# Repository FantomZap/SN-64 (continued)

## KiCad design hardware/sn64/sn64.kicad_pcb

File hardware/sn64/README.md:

# SN 64 KiCad schematic draft

Open **[sn64.kicad_pro](sn64.kicad_pro)** in KiCad 10, then open the schematic. The root (rev `0.4-r3`, A2) holds both cartridge connectors and five child sheets, wired by same-name root labels (the shared net-name contract in [system-integration.md](../../docs/design/system-integration.md#schematic-integration-round-3-2026-09-29)):

- page 2: the [USB programmer child sheet](usb-programmer.kicad_sch) (exports USB_VBUS, USB_3V3, USB_CC1/CC2, jtag_tck/tms/tdi/tdo, TARGET_VREF; R101/R102 DNP because the power sheet's TUSB320 presents Rd);
- page 3: the [SNES cartridge interface child sheet](cart-interface.kicad_sch) (rev 0.3.1-cart: 5 V/3.3 V translators, reset/IRQ/CIC paths, per-pin CIC data translators; see [notes](../../docs/design/cart-interface-schematic.md));
- page 4: the [FPGA child sheet](fpga.kicad_sch) (rev 0.5-fpga, no HDMI pins, designators 4xx: LFE5U-85F CABGA381 with all 381 balls assigned, W25Q128JVSIQ configuration flash, JTAG, SN74CB3Q3384A N64 bus switches; see [notes](../../docs/design/fpga-schematic.md)). Its pin table also generates [interfaces/fpga-pin-map.csv](interfaces/fpga-pin-map.csv) and [fpga/constraints/sn64_board.lpf](../../fpga/constraints/sn64_board.lpf);
- page 5: the [power child sheet](power.kicad_sch) (designators 3xx: host/USB eFuse priority mux, TUSB320, TPS63070 5V_PRE, three TLV62569 FPGA rails, default-off cartridge eFuse and interface switch, monitors; see [notes](../../docs/design/power-schematic.md));
- page 6: the [clock/cartridge-audio child sheet](av-clock.kicad_sch) (draft 0.2-av, designators 7xx: Si5351A + 25 MHz crystal, 25 MHz FPGA oscillator, PCM1808 I2S-master cartridge-audio ADC; the HDMI output of draft 0.1-av was removed on 2026-09-29; see [notes](../../docs/design/av-clock-schematic.md)).

The [PDF](exports/sn64-interface-draft.pdf) is a review export of all six pages; the round-3 export was not visually inspected (no rasteriser available). Project-local libraries hold the symbols KiCad does not ship. It is not a complete electrical design or a manufacturing package.

The SNES socket now lives on its own small board: **[../sn64-socket/](../sn64-socket/)** (generated by [tools/split_socket_board.py](tools/split_socket_board.py); design note [mechanical-architecture.md](../../docs/design/mechanical-architecture.md)). On this main board, J2 is the 2x40 2.00 mm joint header. Check both boards with `tools/verify_socket_joint.py` (and `--negative-test`).

**Board (first draft, 2026-09-29):** [sn64.kicad_pcb](sn64.kicad_pcb) is generated by [tools/build_main_pcb.py](tools/build_main_pcb.py): 6 layers, 1.2 mm, PCBWay-compatible rules, the SummerCart64 lower outline extended to 70 mm above the tongue shoulders, all 410 parts imported with their 530 nets and a connectivity-pulled placement inside block zones (N64 interface at the bottom, FPGA centred with its decoupling underneath, translators under the top joint header with their resistor arrays beneath them, power/USB left, clock/audio right; small passives on the bottom side). DRC after placement (rebuilt 2026-09-29 without the HDMI parts): 0 real errors; the only reports are the USB-C receptacle pads at the board edge (by design; rule exception in `sn64.kicad_dru`) and the N64 fingers' shared solder-mask opening (SummerCart64 footprint).

**Routing draft (2026-09-30):** the tracked board now carries a first autorouted draft ([notes](../../docs/design/pcb-routing.md)): FPGA rotated 180° so its N64 bank faces the bus switches, 240 dog-bone fan-out vias, GND plane on In1, 3.3 V plane on In3, 1.1 V island on In4, signals routed by KiCadRoutingTools (Rust A*, run 2), 157 plane vias, outer GND pours. DRC: no shorts, crossings, clearance or hole violations. **Still open:** 75 signal/power nets (95 connections, mostly in the translator row) and 219 plane pads without a via ([validation/pcb-open-connections.json](validation/pcb-open-connections.json)). Tools: [tools/prepare_route.py](tools/prepare_route.py), [tools/add_plane_vias.py](tools/add_plane_vias.py), [tools/finish_route.py](tools/finish_route.py), [tools/fab-pcbway.txt](tools/fab-pcbway.txt). Rerunning `build_main_pcb.py --force` regenerates the placement and discards this routing. Renders: [top](exports/sn64-pcb-draft-top.png), [bottom](exports/sn64-pcb-draft-bottom.png). Nothing is routed yet; the placement is a starting point, not a reviewed layout.

## What is present

| Item | Contents |
|---|---|
| J1 | 50-contact N64 edge, intended for both original N64 and M64 |
| J2 | Full 62-contact SNES/SFC female socket, including outer contacts and analog audio |
| USB child sheet | J101 JAE USB-C, DNP CC resistors (the power sheet's TUSB320 presents Rd), data/CC ESD arrays, AP2112K-3.3 bridge regulator, FT232HL revision C, 12 MHz crystal, optional DNP EEPROM, SN74AXC4T774 JTAG isolation and J102 target-side service header |
| Symbol library | Editable native KiCad symbols, numbered from the checked pin maps |
| Footprint library | Sanni female-socket and SummerCart64 N64 edge references; local USB component footprints including the reused JAE receptacle geometry |
| Pin maps | [N64](interfaces/n64-pin-map.csv), [SNES](interfaces/snes-pin-map.csv) and [USB circuit nets](interfaces/usb-programmer-net-map.csv) |
| FPGA, power, A/V sheets | See the page list above; authored by [add_fpga_sheet.py](tools/add_fpga_sheet.py), [add_power_sheet.py](tools/add_power_sheet.py) and [add_av_clock_sheet.py](tools/add_av_clock_sheet.py) (deterministic, refuse to overwrite without `--force`), checked by [verify_fpga_sheet.py](tools/verify_fpga_sheet.py), [verify_power_sheet.py](tools/verify_power_sheet.py) and [verify_av_clock_sheet.py](tools/verify_av_clock_sheet.py) |
| Validation | Exported netlist, ERC report, per-sheet checks (interface 31, USB 69, cartridge 20, FPGA 14, power 23, A/V 27) and the [root connectivity check](tools/verify_root_connectivity.py) (4 checks over 141 contract names) |

`GND` is the only net that directly crosses the USB/host-connector boundary. `HOST_3V3`, `HOST_12V`, `SNES_5V_CART`, `USB_VBUS`, `USB_3V3` and `TARGET_VREF` are distinct nets. USB_VBUS also feeds the power sheet's default-off USB input (U302, enabled only when the TUSB320 U301 reports at least 1.5 A and USB_3V3 is present); `TARGET_VREF` comes from FPGA_3V3 through R414 on the FPGA sheet and is not a USB target-power output. The N64 edge reaches the FPGA only through the host-gated bus switches; N64_AUDIO_L/R and the reserved edge contacts stay unconnected. `_N` in net names denotes active low; the cartridge symbols retain the source maps' slash notation.

Connector pins deliberately have the ordinary passive connector type. The CSV and [electrical notes](../../docs/design/snes-interface-notes.md), rather than these pin types, define endpoint direction and special handling. ERC cannot establish drive ownership, voltage tolerance or timing at these pending interfaces.

The USB bridge uses MPSSE JTAG with ACBUS6 controlling the translator's pulled-up, default-disabled `/OE`. The documented host command must include `--status-pin 14`. Its target JTAG nets now reach the ECP5's dedicated JTAG balls on the FPGA sheet (round 3); the configuration flash is loaded through the FPGA. The [programming architecture](../../docs/design/usb-programming-architecture.md) records blank-EEPROM startup, power isolation, persistent-loading requirements and the remaining tests. [Connector and crystal notes](../../docs/design/usb-connector-mechanics.md) record the source geometry and provisional 11 pF crystal load capacitors.

## Reused geometry and its limits

The SNES footprint retains all 62 pads, 2.5 mm ordinary pitch, two 7.5 mm gaps per row, 5 mm row separation, 1.524 mm pads and 0.762 mm drills. A specific purchasable socket, body dimensions and mounting details still need approval before board layout.

The N64 footprint preserves all 50 source pads, 2.5 mm pitch and 1.5 x 7 mm copper dimensions. Pads 1-25 remain on B.Cu and 26-50 on F.Cu. Its origin corresponds to source board coordinates (150,125), so pads are at local Y=6 mm. Six retained `Edge.Cuts` segments form the open lower connector profile, ending at local (±32.25,0) with its bottom at Y=10.5 mm. **Do not duplicate these cuts** when extending the board outline. The footprint does not include a complete board perimeter, mounting holes, layer stack or bevel. Those are separate controlled dimensions in [the geometry record](../../docs/dimensions.md). No generic KiCad board thickness should be treated as the connector thickness.

See [THIRD_PARTY.md](THIRD_PARTY.md), [cartridge provenance](libraries/provenance.json) and [USB provenance](libraries/usb-provenance.json) for sources, modifications and retained licenses. All 24 USB footprint pad objects also match the source geometry in the [footprint review](validation/usb-footprint-review.json). The copies of upstream footprints are reference assets, not a fit-tested SN 64 board.

## Validation and reproducibility

KiCad 10.0.6 exports the six-page schematic to XML and PDF. The round-3 PDF was **not** visually inspected (no rasteriser on this machine); earlier two-sheet exports were. The saved ERC report contains **zero errors** and 10 warnings: 5 `isolated_pin_label` on the reserved N64 edge labels (N64_AUDIO_L/R, N64_KEY1/KEY2_RESERVED, N64_VIDEO_SYNC_RESERVED) and 5 `pin_to_pin` (cartridge U206 unused B4-B8 on the flagged GND). On the integrated root: `verify_cart_interface.py` 20/20 (negative 6/6), `verify_power_sheet.py` 23/23 (negative 11/11), `verify_av_clock_sheet.py` 30/30 (negative 12/12), `verify_fpga_sheet.py` **12/13** (negative 10/10; the failing check is `efuse_fault_n`, a 5V_PRE divider on ball K4, an open owner decision in [system-integration.md](../../docs/design/system-integration.md)), `verify_root_connectivity.py` 4/4 (negative 4/4). The schematic is incomplete and is not an ERC-clean release. Rerun checks as circuitry changes.

The [independent validation script](tools/verify_interfaces.py) checks the exported connector pin/net assignments against the separately researched maps, rejects accidental cross-domain connections, and compares both footprints against the original downloaded sources. The corresponding [result](validation/interface-check.json) and [review](validation/interface-review.md) record the result and remaining limitations.

The saved reports record **30 cartridge-interface checks passed and 69 USB checks passed, with zero failed checks** (the USB set now also checks the DNP CC resistors and the CC/VBUS/USB_3V3/JTAG/TARGET_VREF exports). The [USB validator](tools/verify_usb_programmer.py) independently exports the schematic and compares it with fixed manufacturer pin tables, checking all USB component pins, rail separation, CC/data/ESD connections, bridge support, JTAG directions and disabled startup. See its [result](validation/usb-check.json) and [review](validation/usb-review.md). These are static checks; no USB enumeration, clock measurement, suspend-current measurement, programming, cold boot, electrical protection or compatibility test has been performed on SN 64 hardware.

To regenerate review files after editing, run these from this directory with KiCad's CLI on PATH:

```powershell
kicad-cli sch export netlist --format kicadxml -o validation/sn64.xml sn64.kicad_sch
kicad-cli sch export pdf -o exports/sn64-interface-draft.pdf sn64.kicad_sch
kicad-cli sch erc --format json --output validation/erc.json --exit-code-violations sn64.kicad_sch
```

The per-sheet and root checks, from the repository root with KiCad's Python (each also takes `--negative-test`, except the interface and USB validators):

```powershell
$py = 'C:\Program Files\KiCad\10.0\bin\python.exe'; $cli = 'C:\Program Files\KiCad\10.0\bin\kicad-cli.exe'
& $py hardware/sn64/tools/verify_interfaces.py --source-root . --kicad-cli $cli
& $py hardware/sn64/tools/verify_usb_programmer.py --kicad-cli $cli
& $py hardware/sn64/tools/verify_cart_interface.py --kicad-cli $cli
& $py hardware/sn64/tools/verify_fpga_sheet.py --kicad-cli $cli --lattice-csv <ECP5U-85 pinout CSV> --datasheets <dir>
& $py hardware/sn64/tools/verify_power_sheet.py --kicad-cli $cli
& $py hardware/sn64/tools/verify_av_clock_sheet.py --project hardware/sn64 --kicad-cli $cli
& $py hardware/sn64/tools/verify_root_connectivity.py --kicad-cli $cli
```

The initial authoring script, [create_interface_draft.py](tools/create_interface_draft.py), uses KiCad's Python and downloaded upstream sources. It refuses to replace an existing schematic unless explicitly passed `--force`. Once circuit editing begins, edit the native KiCad files; do not regenerate the initial sheet over the circuit work.

[add_usb_programmer.py](tools/add_usb_programmer.py) records how the initial USB sheet was authored from the reference designs and installed KiCad libraries. It also refuses to replace its sheet without `--force`; use native KiCad editing for subsequent development. Regeneration requires `--source-root <original-project-with-downloads>` and `--kicad-share <KiCad-share-directory>`, and intentionally replaces the entire USB child sheet when forced.

## Remaining integration

**Required in the first revision:** a side-mounted USB-C data/programming port and matching enclosure opening, supporting initial firmware/FPGA loading, updates and recovery without successful host-console boot. The bridge and service-access circuit now exists; the complete programming path remains pending target integration and testing. Final side-port placement, cable access and shell clearances remain mechanical work.

1. Build the power budget for the FPGA, memory, digital A/V and real cartridges on both hosts. The M64 reference annotates a 500 mA cartridge limiter; that is not a guaranteed SN 64 allowance. There is no 5 V N64 edge supply. Select input power, no-backfeed paths and default-off protected cartridge power from the actual budget.
2. Adapt the sd2snes translator circuit using the [reuse review](../../docs/design/translation-reuse-review.md). Reverse address/strobe ownership for a console endpoint; define enable, read/write turnaround and power-off behavior for the exact part. Separately implement IRQ/reset, CIC, expansion and analog audio.
3. Integrate the reusable SNES FPGA core, physical cartridge bridge and N64 endpoint. Select FPGA/package and memory only after resource, I/O, clock and timing evidence. Connect the USB programmer to the selected target and persistent configuration storage, define programming power/boot straps and package the loading/recovery software. Add health monitoring and A/V, then review the complete schematic.
4. Place and route a PCB with the verified mechanical constraints; develop the FreeCAD enclosure around that assembly. Produce PCBWay files after electrical review and prototype/fit validation.

These are stages of the full specification. PAL, protection, save integrity, telemetry, factory testing and all remaining specification targets are retained. Video and audio go to the console over the cartridge bus (console video path); the adapter has no output of its own. No PCB layout, FPGA bitstream, working adapter, print-ready shell or PCBWay manufacturing release is included in this revision.

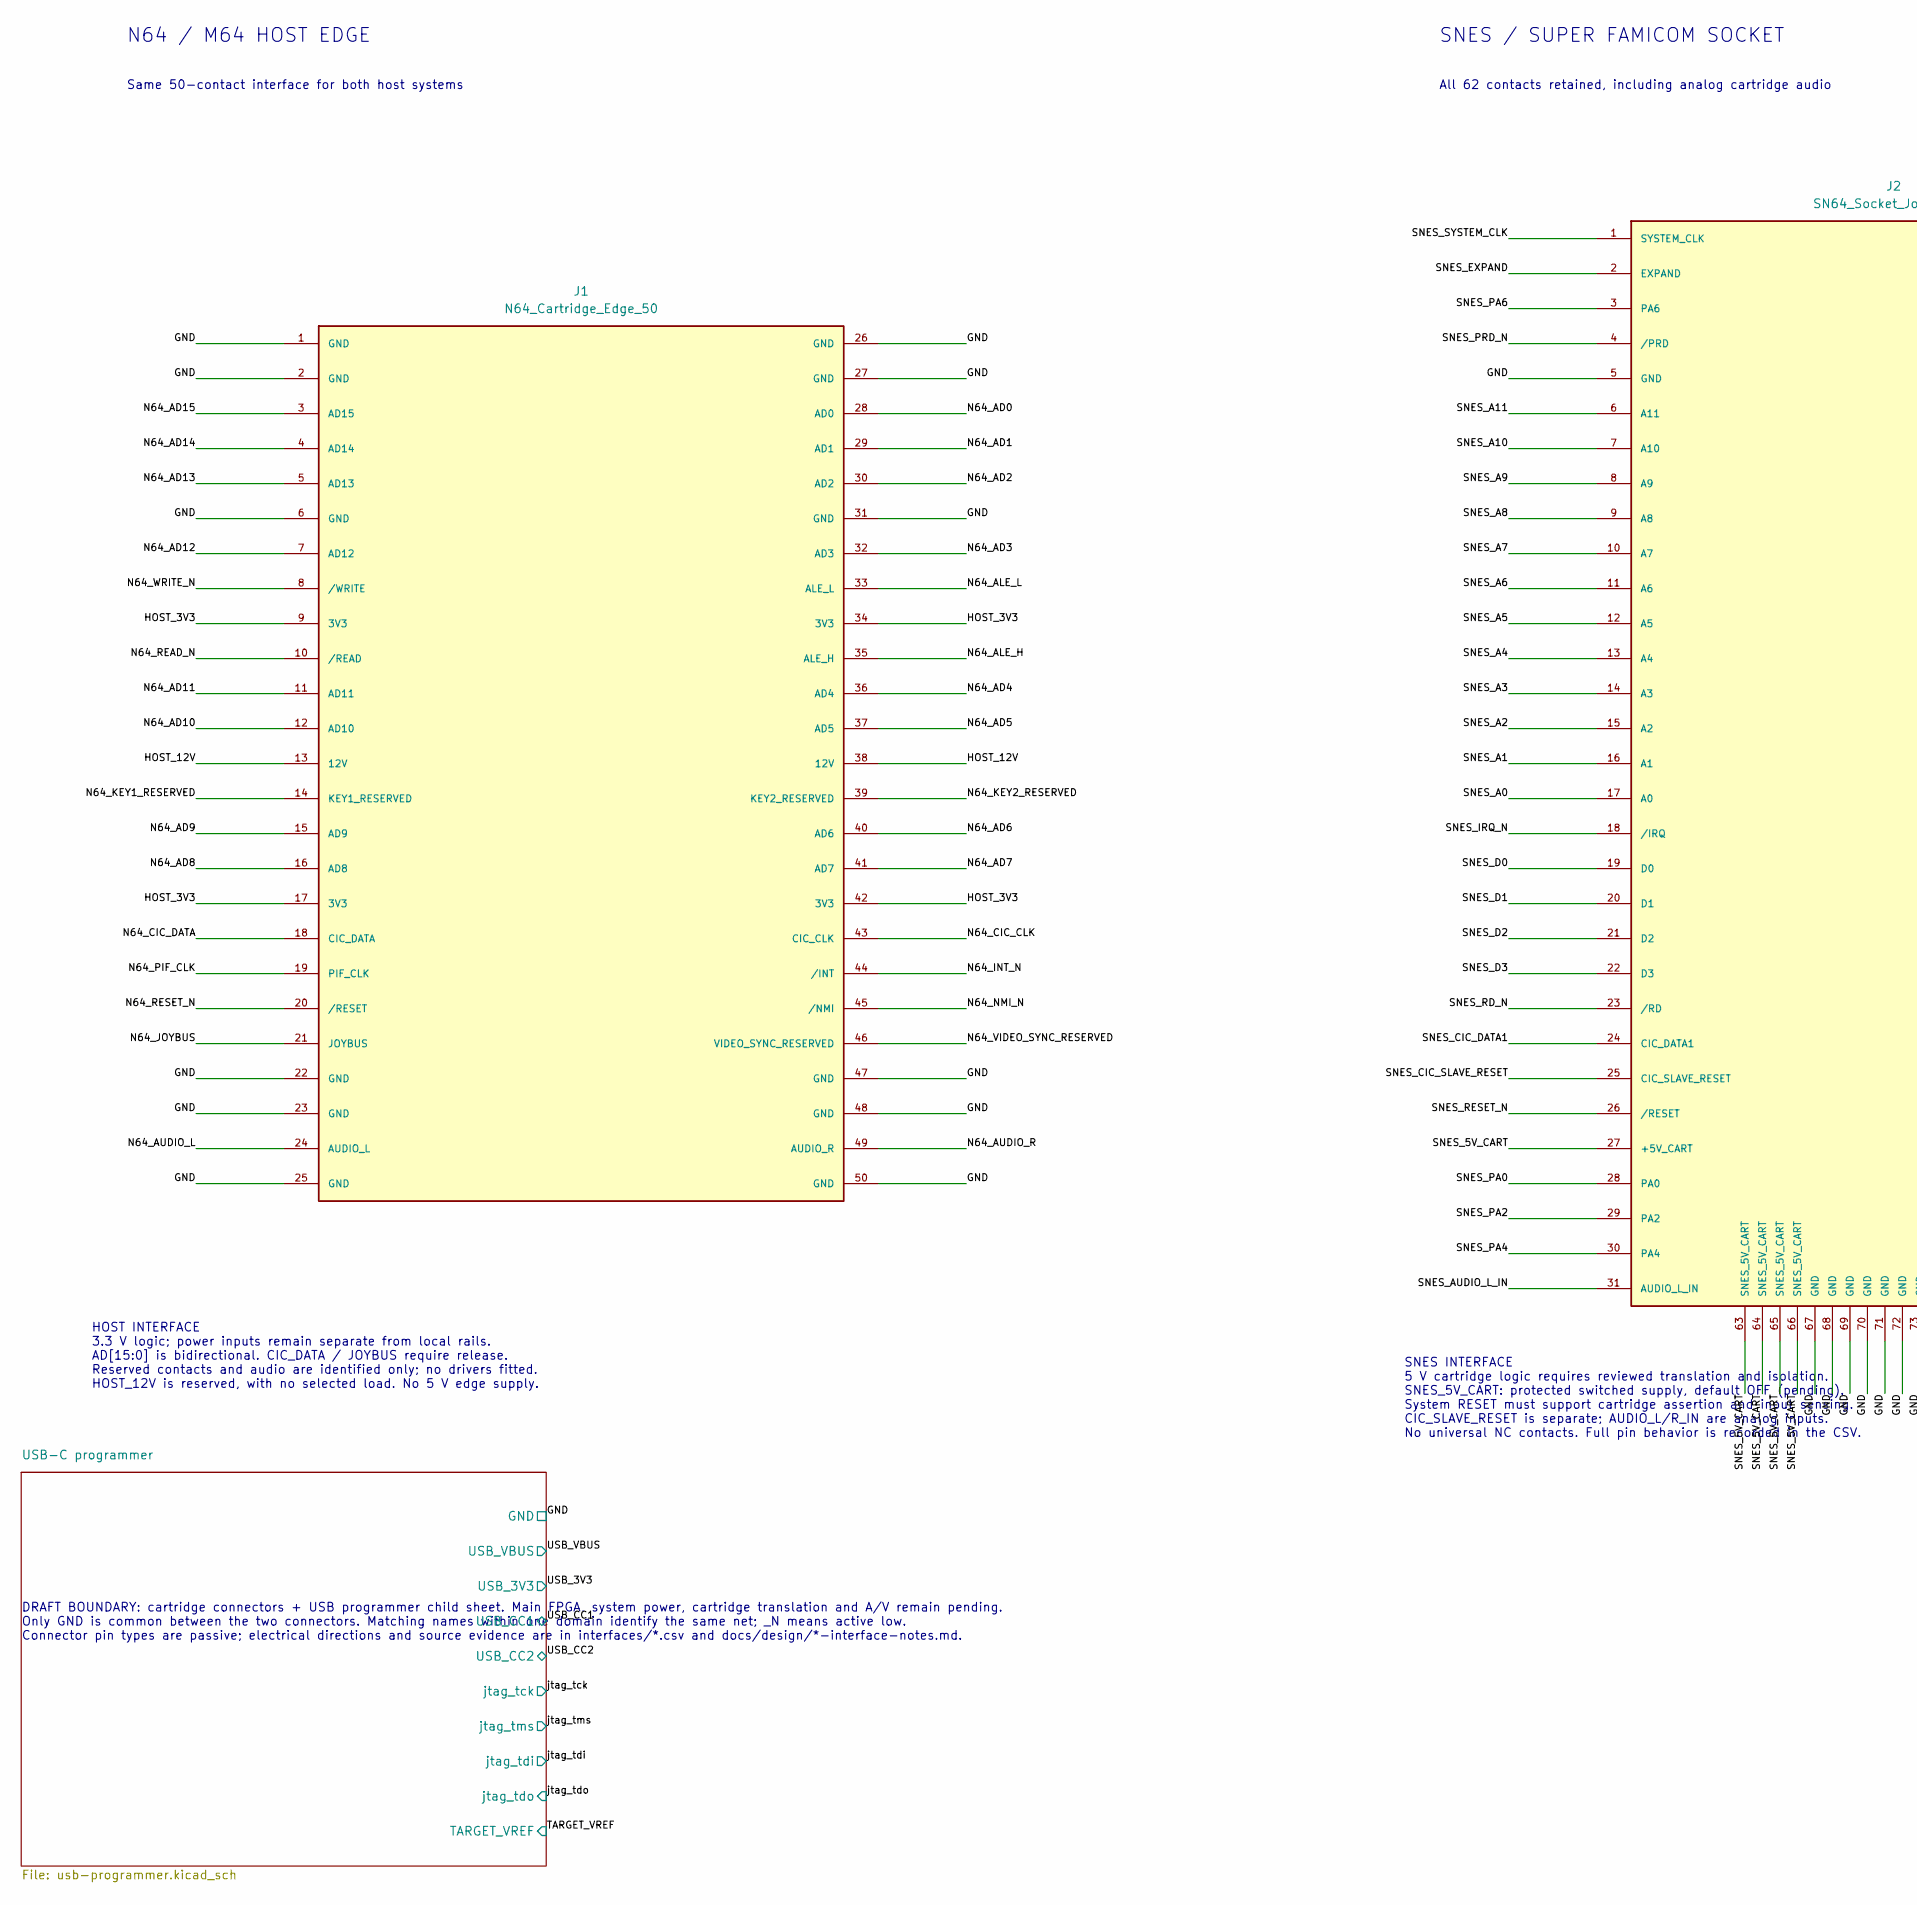
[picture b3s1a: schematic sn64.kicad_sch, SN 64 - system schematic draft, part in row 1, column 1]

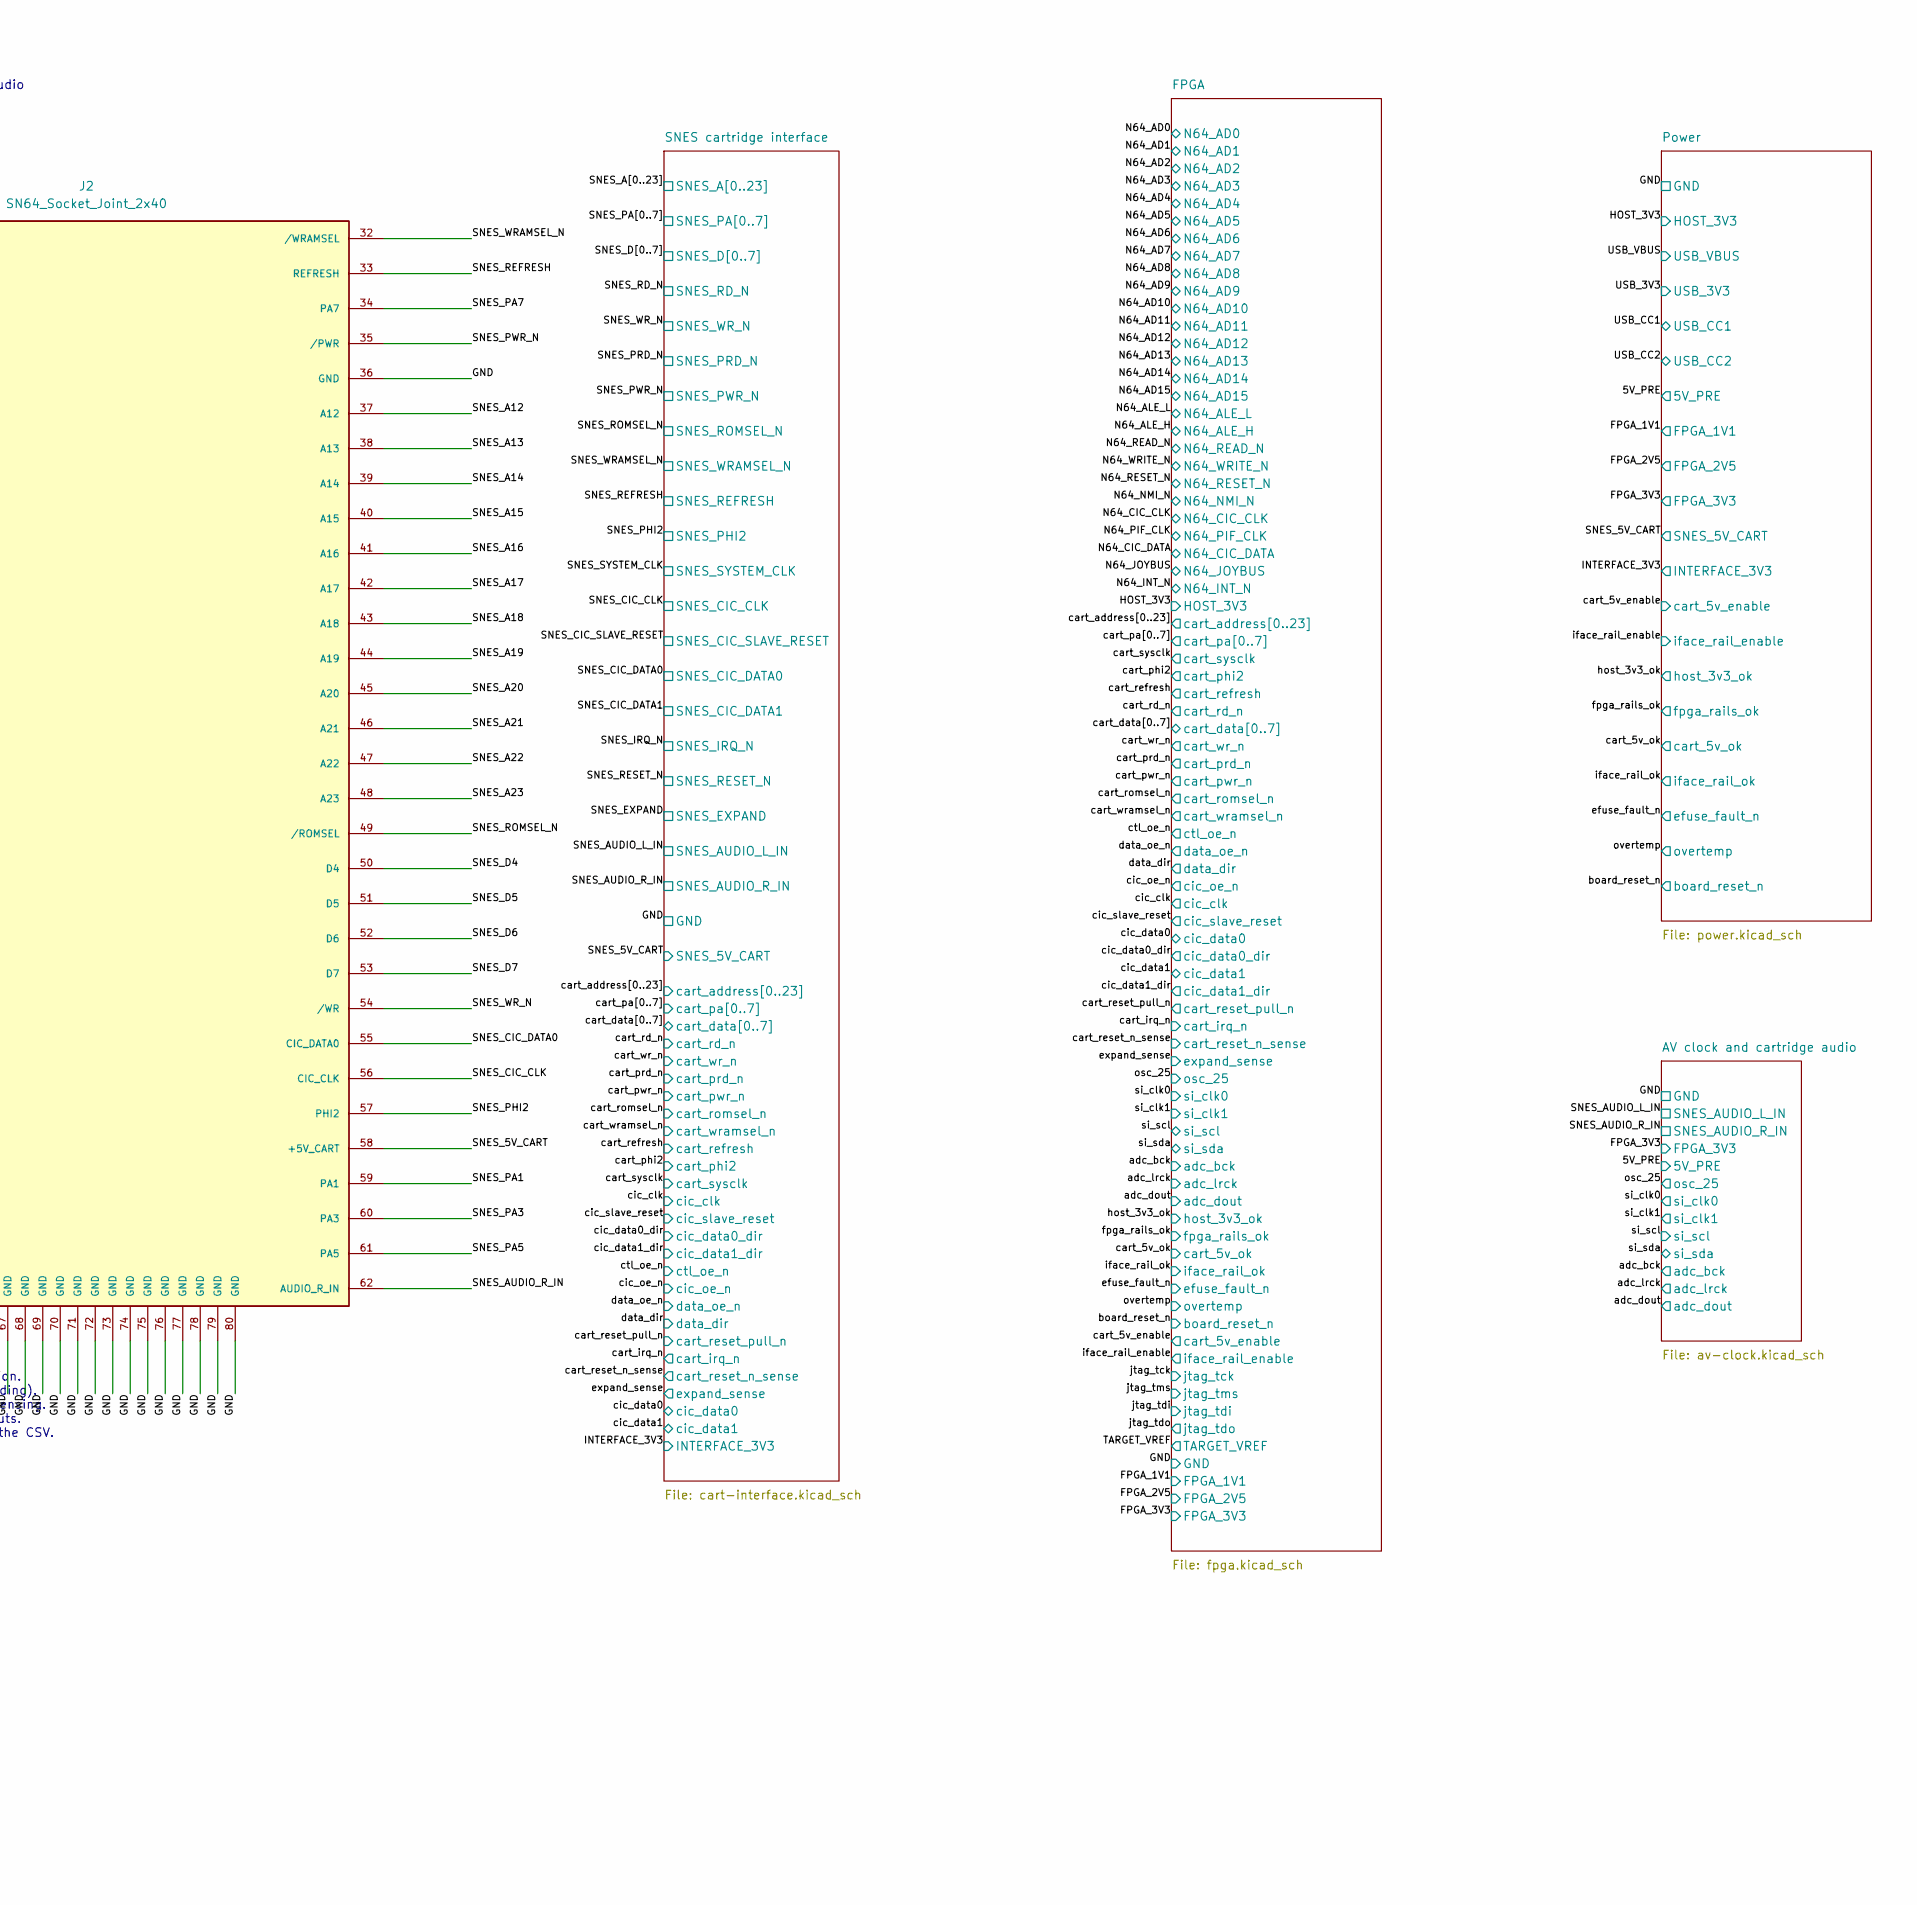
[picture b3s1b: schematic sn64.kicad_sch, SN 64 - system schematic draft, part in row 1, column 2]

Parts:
J1: N64_Cartridge_Edge_50; N64_Edge_SC64_Reference
J2: SN64_Socket_Joint_2x40; PinHeader_2x40_P2.00mm_Horizontal

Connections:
/GND: J1.1 (GND), J1.2 (GND), J1.6 (GND), J1.22 (GND), J1.23 (GND), J1.25 (GND), J1.26 (GND), J1.27 (GND), J1.31 (GND), J1.47 (GND), J1.48 (GND), J1.50 (GND), J2.5 (GND), J2.36 (GND), J2.67 (GND), J2.68 (GND), J2.69 (GND), J2.70 (GND), J2.71 (GND), J2.72 (GND), J2.73 (GND), J2.74 (GND), J2.75 (GND), J2.76 (GND), J2.77 (GND), J2.78 (GND), J2.79 (GND), J2.80 (GND); also elsewhere on the board
/HOST_3V3: J1.9 (3V3), J1.17 (3V3), J1.34 (3V3), J1.42 (3V3); also elsewhere on the board
/HOST_12V: J1.13 (12V), J1.38 (12V)
/N64_AD0: J1.28 (AD0); also elsewhere on the board
/N64_AD1: J1.29 (AD1); also elsewhere on the board
/N64_AD2: J1.30 (AD2); also elsewhere on the board
/N64_AD3: J1.32 (AD3); also elsewhere on the board
/N64_AD4: J1.36 (AD4); also elsewhere on the board
/N64_AD5: J1.37 (AD5); also elsewhere on the board
/N64_AD6: J1.40 (AD6); also elsewhere on the board
/N64_AD7: J1.41 (AD7); also elsewhere on the board
/N64_AD8: J1.16 (AD8); also elsewhere on the board
/N64_AD9: J1.15 (AD9); also elsewhere on the board
/N64_AD10: J1.12 (AD10); also elsewhere on the board
/N64_AD11: J1.11 (AD11); also elsewhere on the board
/N64_AD12: J1.7 (AD12); also elsewhere on the board
/N64_AD13: J1.5 (AD13); also elsewhere on the board
/N64_AD14: J1.4 (AD14); also elsewhere on the board
/N64_AD15: J1.3 (AD15); also elsewhere on the board
/N64_ALE_H: J1.35 (ALE_H); also elsewhere on the board
/N64_ALE_L: J1.33 (ALE_L); also elsewhere on the board
/N64_AUDIO_L: J1.24 (AUDIO_L)
/N64_AUDIO_R: J1.49 (AUDIO_R)
/N64_CIC_CLK: J1.43 (CIC_CLK); also elsewhere on the board
/N64_CIC_DATA: J1.18 (CIC_DATA); also elsewhere on the board
/N64_INT_N: J1.44 (/INT); also elsewhere on the board
/N64_JOYBUS: J1.21 (JOYBUS); also elsewhere on the board
/N64_KEY1_RESERVED: J1.14 (KEY1_RESERVED)
/N64_KEY2_RESERVED: J1.39 (KEY2_RESERVED)
/N64_NMI_N: J1.45 (/NMI); also elsewhere on the board
/N64_PIF_CLK: J1.19 (PIF_CLK); also elsewhere on the board
/N64_READ_N: J1.10 (/READ); also elsewhere on the board
/N64_RESET_N: J1.20 (/RESET); also elsewhere on the board
/N64_VIDEO_SYNC_RESERVED: J1.46 (VIDEO_SYNC_RESERVED)
/N64_WRITE_N: J1.8 (/WRITE); also elsewhere on the board
/SNES_5V_CART: J2.27 (+5V_CART), J2.58 (+5V_CART), J2.63 (SNES_5V_CART), J2.64 (SNES_5V_CART), J2.65 (SNES_5V_CART), J2.66 (SNES_5V_CART); also elsewhere on the board
/SNES_A0: J2.17 (A0); also elsewhere on the board
/SNES_A1: J2.16 (A1); also elsewhere on the board
/SNES_A2: J2.15 (A2); also elsewhere on the board
/SNES_A3: J2.14 (A3); also elsewhere on the board
/SNES_A4: J2.13 (A4); also elsewhere on the board
/SNES_A5: J2.12 (A5); also elsewhere on the board
/SNES_A6: J2.11 (A6); also elsewhere on the board
/SNES_A7: J2.10 (A7); also elsewhere on the board
/SNES_A8: J2.9 (A8); also elsewhere on the board
/SNES_A9: J2.8 (A9); also elsewhere on the board
/SNES_A10: J2.7 (A10); also elsewhere on the board
/SNES_A11: J2.6 (A11); also elsewhere on the board
/SNES_A12: J2.37 (A12); also elsewhere on the board
/SNES_A13: J2.38 (A13); also elsewhere on the board
/SNES_A14: J2.39 (A14); also elsewhere on the board
/SNES_A15: J2.40 (A15); also elsewhere on the board
/SNES_A16: J2.41 (A16); also elsewhere on the board
/SNES_A17: J2.42 (A17); also elsewhere on the board
/SNES_A18: J2.43 (A18); also elsewhere on the board
/SNES_A19: J2.44 (A19); also elsewhere on the board
/SNES_A20: J2.45 (A20); also elsewhere on the board
/SNES_A21: J2.46 (A21); also elsewhere on the board
/SNES_A22: J2.47 (A22); also elsewhere on the board
/SNES_A23: J2.48 (A23); also elsewhere on the board
/SNES_AUDIO_L_IN: J2.31 (AUDIO_L_IN); also elsewhere on the board
/SNES_AUDIO_R_IN: J2.62 (AUDIO_R_IN); also elsewhere on the board
/SNES_CIC_CLK: J2.56 (CIC_CLK); also elsewhere on the board
/SNES_CIC_DATA0: J2.55 (CIC_DATA0); also elsewhere on the board
/SNES_CIC_DATA1: J2.24 (CIC_DATA1); also elsewhere on the board
/SNES_CIC_SLAVE_RESET: J2.25 (CIC_SLAVE_RESET); also elsewhere on the board
/SNES_D0: J2.19 (D0); also elsewhere on the board
/SNES_D1: J2.20 (D1); also elsewhere on the board
/SNES_D2: J2.21 (D2); also elsewhere on the board
/SNES_D3: J2.22 (D3); also elsewhere on the board
/SNES_D4: J2.50 (D4); also elsewhere on the board
/SNES_D5: J2.51 (D5); also elsewhere on the board
/SNES_D6: J2.52 (D6); also elsewhere on the board
/SNES_D7: J2.53 (D7); also elsewhere on the board
/SNES_EXPAND: J2.2 (EXPAND); also elsewhere on the board
/SNES_IRQ_N: J2.18 (/IRQ); also elsewhere on the board
/SNES_PA0: J2.28 (PA0); also elsewhere on the board
/SNES_PA1: J2.59 (PA1); also elsewhere on the board
/SNES_PA2: J2.29 (PA2); also elsewhere on the board
/SNES_PA3: J2.60 (PA3); also elsewhere on the board
/SNES_PA4: J2.30 (PA4); also elsewhere on the board
/SNES_PA5: J2.61 (PA5); also elsewhere on the board
/SNES_PA6: J2.3 (PA6); also elsewhere on the board
/SNES_PA7: J2.34 (PA7); also elsewhere on the board
/SNES_PHI2: J2.57 (PHI2); also elsewhere on the board
/SNES_PRD_N: J2.4 (/PRD); also elsewhere on the board
/SNES_PWR_N: J2.35 (/PWR); also elsewhere on the board
/SNES_RD_N: J2.23 (/RD); also elsewhere on the board
/SNES_REFRESH: J2.33 (REFRESH); also elsewhere on the board
/SNES_RESET_N: J2.26 (/RESET); also elsewhere on the board
/SNES_ROMSEL_N: J2.49 (/ROMSEL); also elsewhere on the board
/SNES_SYSTEM_CLK: J2.1 (SYSTEM_CLK); also elsewhere on the board
/SNES_WRAMSEL_N: J2.32 (/WRAMSEL); also elsewhere on the board
/SNES_WR_N: J2.54 (/WR); also elsewhere on the board

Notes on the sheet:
N64 / M64 HOST EDGE
SNES / SUPER FAMICOM SOCKET
Same 50-contact interface for both host systems
All 62 contacts retained, including analog cartridge audio
HOST INTERFACE 3.3 V logic; power inputs remain separate from local rails. AD[15:0] is bidirectional. CIC_DATA / JOYBUS require release. Reserved contacts and audio are identified only; no drivers fitted. HOST_12V is reserved, with no selected load. No 5 V edge supply.
SNES INTERFACE 5 V cartridge logic requires reviewed translation and isolation. SNES_5V_CART: protected switched supply, default OFF (pending). System RESET must support cartridge assertion and input sensing. CIC_SLAVE_RESET is separate; AUDIO_L/R_IN are analog inputs. No universal NC contacts. Ful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
DRAFT BOUNDARY: cartridge connectors + USB programmer child sheet. Main FPGA, system power, cartridge translation and A/V remain pending. Only GND is common between the two connectors. Matching names within one domain identify the same net; _N means active low. Connector pin types are passive; elec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
